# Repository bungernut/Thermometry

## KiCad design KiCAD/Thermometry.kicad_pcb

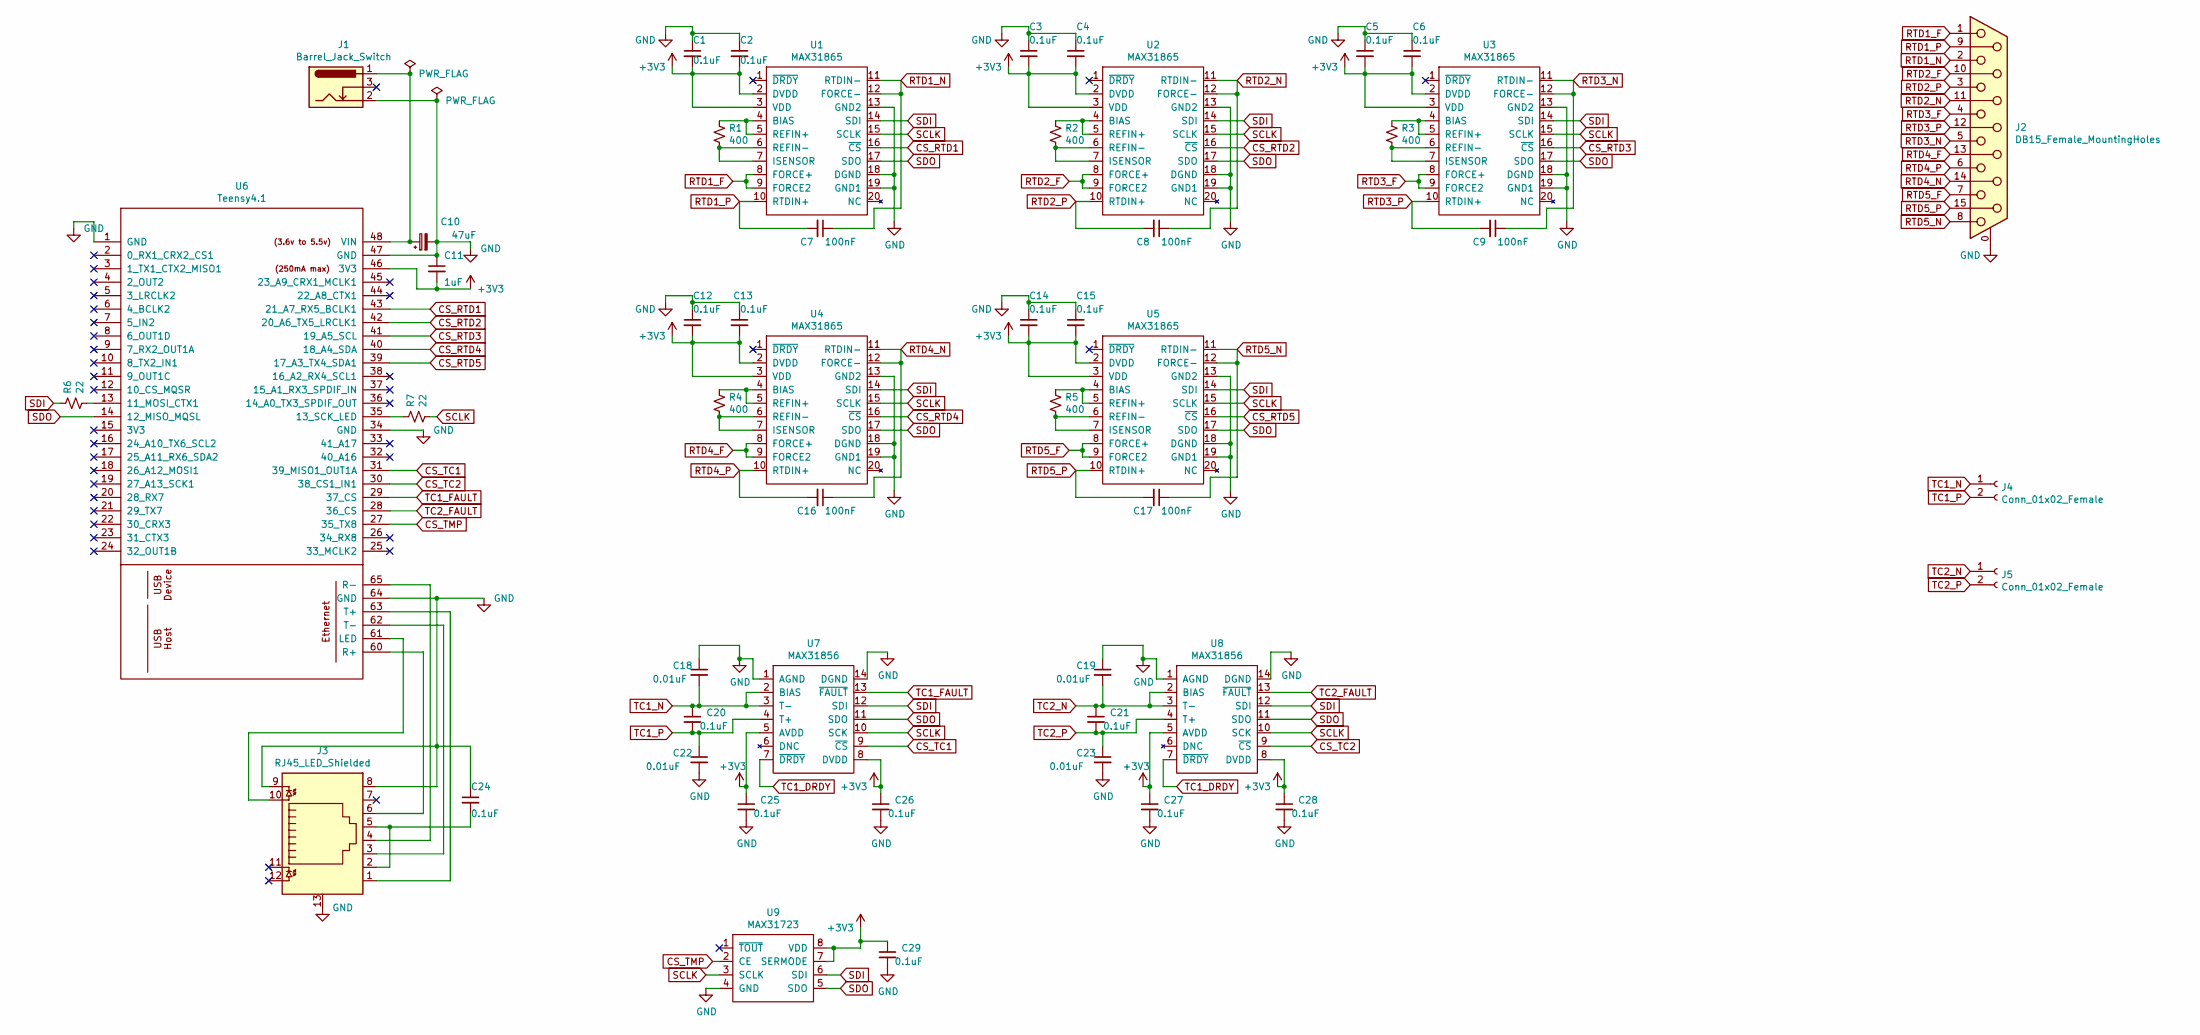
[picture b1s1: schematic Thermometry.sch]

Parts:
C1, C2, C3, C4, C5, C6, C12, C13, C14, C15, C20, C21, C24, C25, C26, C27, C28, C29: 0.1uF; C_0805_2012Metric_Pad1.18x1.45mm_HandSolder
C7, C8, C9, C16, C17: 100nF; C_0805_2012Metric_Pad1.18x1.45mm_HandSolder
C10: 47uF; CP_Radial_D5.0mm_P2.00mm
C11: 1uF; C_0805_2012Metric_Pad1.18x1.45mm_HandSolder
C18, C19, C22, C23: 0.01uF; C_0805_2012Metric_Pad1.18x1.45mm_HandSolder
J1: Barrel_Jack_Switch; BarrelJack_Horizontal; DigikeyPN CP-002A-ND
J2: DB15_Female_MountingHoles; DSUB-15_Male_Horizontal_P2.77x2.84mm_EdgePinOffset4.94mm_Ho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
J3: RJ45_LED_Shielded; RJ45_Cetus_J1B1211CCD_Horizontal; DigikeyPN 1278-1052-ND
J4, J5: Conn_01x02_Female; SolderWire-0.15sqmm_1x02_P4mm_D0.5mm_OD1.5mm
R1, R2, R3, R4, R5: 400; R_1206_3216Metric_Pad1.30x1.75mm_HandSolder; DigikeyPN 13-RT1206BRD07400RLCT-ND
R6, R7: 22; R_0805_2012Metric_Pad1.20x1.40mm_HandSolder; DigikeyPN 13-RT1206BRD07400RLCT-ND
U1, U2, U3, U4, U5: MAX31865; DigikeyPN MAX31865AAP+TCT-ND
U6: Teensy4.1; Teensy41
U7, U8: MAX31856; DigikeyPN MAX31856MUD+TCT-ND
U9: MAX31723; MAX3172X

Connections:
+3V3: C1.2, C2.2, C3.2, C4.2, C5.2, C6.2, C11.2, C12.2, C13.2, C14.2, C15.2, C25.1, C26.1, C27.1, C28.1, C29.1, U1.2 (DVDD), U1.3 (VDD), U2.2 (DVDD), U2.3 (VDD), U3.2 (DVDD), U3.3 (VDD), U4.2 (DVDD), U4.3 (VDD), U5.2 (DVDD), U5.3 (VDD), U6.46 (3V3), U7.5 (AVDD), U7.8 (DVDD), U8.5 (AVDD), U8.8 (DVDD), U9.7 (SERMODE), U9.8 (VDD)
CS_RTD1: U1.16 (~CS), U6.43 (21_A7_RX5_BCLK1)
CS_RTD2: U2.16 (~CS), U6.42 (20_A6_TX5_LRCLK1)
CS_RTD3: U3.16 (~CS), U6.41 (19_A5_SCL)
CS_RTD4: U4.16 (~CS), U6.40 (18_A4_SDA)
CS_RTD5: U5.16 (~CS), U6.39 (17_A3_TX4_SDA1)
CS_TC1: U6.31 (39_MISO1_OUT1A), U7.9 (~CS)
CS_TC2: U6.30 (38_CS1_IN1), U8.9 (~CS)
CS_TMP: U6.27 (35_TX8), U9.2 (CE)
GND: C1.1, C2.1, C3.1, C4.1, C5.1, C6.1, C10.2, C11.1, C12.1, C13.1, C14.1, C15.1, C18.1, C19.1, C22.2, C23.2, C24.1, C25.2, C26.2, C27.2, C28.2, C29.2, J1.2, J2.0 (PAD), J3.8, J3.9, J3.13, U1.13 (GND2), U1.18 (DGND), U1.19 (GND1), U2.13 (GND2), U2.18 (DGND), U2.19 (GND1), U3.13 (GND2), U3.18 (DGND), U3.19 (GND1), U4.13 (GND2), U4.18 (DGND), U4.19 (GND1), U5.13 (GND2), U5.18 (DGND), U5.19 (GND1), U6.1 (GND), U6.34 (GND), U6.47 (GND), U6.64 (GND), U7.1 (AGND), U7.14 (DGND), U8.1 (AGND), U8.14 (DGND), U9.4 (GND)
unnamed: C10.1, J1.1, U6.48 (VIN)
unnamed: C24.2, J3.2, J3.5
unnamed: J3.1, U6.63 (T+)
unnamed: J3.3, U6.62 (T-)
unnamed: J3.4, U6.65 (R-)
unnamed: J3.6, U6.60 (R+)
unnamed: J3.10, U6.61 (LED)
unnamed: R1.1, U1.4 (BIAS), U1.5 (REFIN+)
unnamed: R1.2, U1.6 (REFIN-), U1.7 (ISENSOR)
unnamed: R2.1, U2.4 (BIAS), U2.5 (REFIN+)
unnamed: R2.2, U2.6 (REFIN-), U2.7 (ISENSOR)
unnamed: R3.1, U3.4 (BIAS), U3.5 (REFIN+)
unnamed: R3.2, U3.6 (REFIN-), U3.7 (ISENSOR)
unnamed: R4.1, U4.4 (BIAS), U4.5 (REFIN+)
unnamed: R4.2, U4.6 (REFIN-), U4.7 (ISENSOR)
unnamed: R5.1, U5.4 (BIAS), U5.5 (REFIN+)
unnamed: R5.2, U5.6 (REFIN-), U5.7 (ISENSOR)
unnamed: R6.2, U6.13 (11_MOSI_CTX1)
unnamed: R7.1, U6.35 (13_SCK_LED)
RTD1_F: J2.1, U1.8 (FORCE+), U1.9 (FORCE2)
RTD1_N: C7.1, J2.2, U1.11 (RTDIN-), U1.12 (FORCE-)
RTD1_P: C7.2, J2.9, U1.10 (RTDIN+)
RTD2_F: J2.10, U2.8 (FORCE+), U2.9 (FORCE2)
RTD2_N: C8.1, J2.11 (P111), U2.11 (RTDIN-), U2.12 (FORCE-)
RTD2_P: C8.2, J2.3, U2.10 (RTDIN+)
RTD3_F: J2.4, U3.8 (FORCE+), U3.9 (FORCE2)
RTD3_N: C9.1, J2.5, U3.11 (RTDIN-), U3.12 (FORCE-)
RTD3_P: C9.2, J2.12, U3.10 (RTDIN+)
RTD4_F: J2.13, U4.8 (FORCE+), U4.9 (FORCE2)
RTD4_N: C16.1, J2.14, U4.11 (RTDIN-), U4.12 (FORCE-)
RTD4_P: C16.2, J2.6, U4.10 (RTDIN+)
RTD5_F: J2.7, U5.8 (FORCE+), U5.9 (FORCE2)
RTD5_N: C17.1, J2.8, U5.11 (RTDIN-), U5.12 (FORCE-)
RTD5_P: C17.2, J2.15, U5.10 (RTDIN+)
SCLK: R7.2, U1.15 (SCLK), U2.15 (SCLK), U3.15 (SCLK), U4.15 (SCLK), U5.15 (SCLK), U7.10 (SCK), U8.10 (SCK), U9.3 (SCLK)
SDI: R6.1, U1.14 (SDI), U2.14 (SDI), U3.14 (SDI), U4.14 (SDI), U5.14 (SDI), U7.12 (SDI), U8.12 (SDI), U9.6 (SDI)
SDO: U1.17 (SDO), U2.17 (SDO), U3.17 (SDO), U4.17 (SDO), U5.17 (SDO), U6.14 (12_MISO_MQSL), U7.11 (SDO), U8.11 (SDO), U9.5 (SDO)
TC1_DRDY: U7.7 (~DRDY), U8.7 (~DRDY)
TC1_FAULT: U6.29 (37_CS), U7.13 (~FAULT)
TC1_N: C18.2, C20.1, J4.1, U7.2 (BIAS), U7.3 (T-)
TC1_P: C20.2, C22.1, J4.2, U7.4 (T+)
TC2_FAULT: U6.28 (36_CS), U8.13 (~FAULT)
TC2_N: C19.2, C21.1, J5.1, U8.2 (BIAS), U8.3 (T-)
TC2_P: C21.2, C23.1, J5.2, U8.4 (T+)

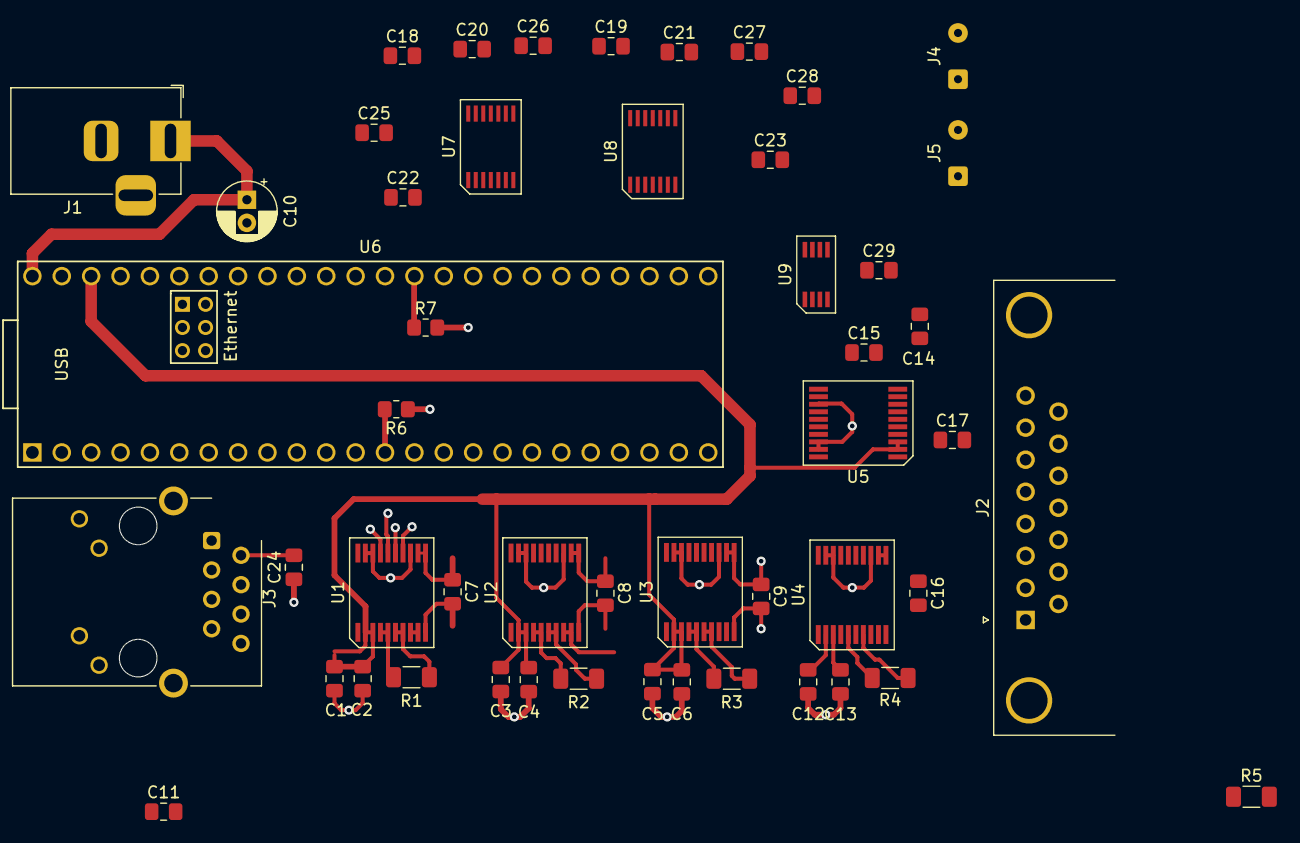
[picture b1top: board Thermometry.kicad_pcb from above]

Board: 4 copper layers, 50 parts (0 on the bottom side), 54 nets.

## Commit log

2021-09-12 initial commit with sch
2021-09-12 updated sch and netlists for PCB placements
2021-09-13 routing progress
